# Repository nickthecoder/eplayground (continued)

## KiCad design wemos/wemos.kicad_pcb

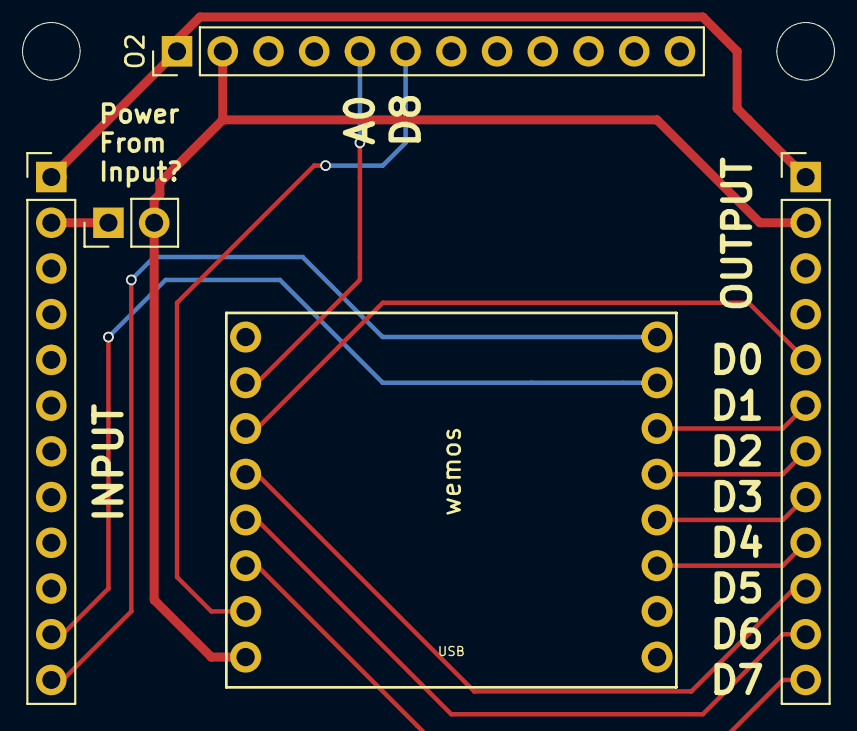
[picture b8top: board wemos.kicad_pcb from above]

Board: 2 copper layers, 7 parts (0 on the bottom side), 16 nets.

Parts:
I1: SerialInput; Socket_Strip_Straight_1x12_Pitch2.54mm
M3, M3#2: MountingHole_3.2mm_M3
O1, O2: Output; Socket_Strip_Straight_1x12_Pitch2.54mm
SW1: SW_SPST; Pin_Header_Straight_1x02_Pitch2.54mm
U1: wemos

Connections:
/A0: O2.5, U1.10
/D0: O1.5, U1.11
/D1: O1.6, U1.6
/D2: O1.7, U1.5
/D3: O1.8, U1.4
/D4: O1.9, U1.3
/D5: O1.10, U1.12
/D6: O1.11, U1.13
/D7: O1.12, U1.14
/D8: O2.6, U1.15
/GND: I1.3, O1.3, O2.3, U1.2
/RX: I1.11, U1.7
/TX: I1.12, U1.8
/VCC: O1.2, O2.2, SW1.2, U1.16
/VIN: I1.1, O1.1, O2.1
unnamed: I1.2, SW1.1

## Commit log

2018-03-31 Added Pro Mini and Nano boards, and power connector.
2018-03-31 Ignoring the library downloaded from github
2018-03-31 Made more room for bare AT chip's crystal.
2018-03-31 Added edge cuts. Plus minor tweaks.
2018-04-01 First version nearly complete, but I'm not happy with it, so I'm going to redsign the layout from scratch.
2018-04-01 Reworked the circuit from scratch.
2018-04-02 Tidy up - Note, there is a problem with VIN.
2018-04-02 More tweaking of the layout.
2018-04-02 Replaced surface mount LEDs with rectangular through hole. Removed PRO-Mini FTDI Header pins from the footprint.
2018-04-02 Fix board size, and moved I2C headers.
2018-04-02 Moved output headers in slightly. Improved text.
2018-04-02 Incfreased resistor size. Improved the ProMini footprint. Removed the VCC LED.
2018-04-02 Changed the directory structure.
2018-04-02 Created a blank and buttons module.
2018-04-02 Tidied up old thinner tracks.
2018-04-03 Sent buttons to DirtyPCB for manufacturing.
2018-04-03 Added a MCP23017 I2C IO Expansion module.
2018-04-04 Added a new "power" and LEDs module (split into two half size modules)
2018-04-04 Tidied up blank, and removed the voltage regulator from "power" module.
2018-04-04 Reworked the ditduino.
2018-04-04 Reworked diyduino module.
2018-04-04 Tidied diyduino
2018-04-04 Added an extra FTDI header, with the RX and TX reversed.
2018-04-04 Reordered serial connectors so that A4 and A5 on the analog connector are in the same place as they are on the serial connector.
2018-04-04 Created blankHalf
2018-04-04 Added buttons and pots modules.
2018-04-05 Combined multiples modules into a single board (called combined).
2018-04-06 Created shift register module (which can act as a master or a slave).
2018-04-06 Rotated the shift register, re-routed the power lines, and added the option of output-enable.
2018-04-06 Created a "prototype" module.
2018-04-06 Reworked the MCP23017 I2C IO Expander module.
2018-04-07 Rotated the TO-220 MOSFETs for better heat dissipation.
2018-04-08 Added a "Blue Pill" module.
2018-04-08 Finished the Blue Pill module.
2018-04-09 "Other" output can have its VCC switched between 5V and 3.3V.
2018-04-09 Rerouted "Serial 2" on Blue Pill module
2018-04-09 Added WeMos module.
2018-04-09 Added Level Converter module.
2018-04-10 Added a multiplexer module (which works in master and slave mode, for up to 40:1 with 5 boards)
2018-04-10 Added I2C header board, which also has an "SPI" OLED header.
2018-04-10 Added a MAX7219 module, which with 8 of the 16 key inputs, and header pins for a 8x6 LED matrix.
2018-04-30 Improved ioExpansion
2018-04-30 Added extra I2C headers to the ioExpansion module.
2018-04-30 Tweaked shift-595
2018-04-30 Reworked shift-595 to include 2 banks of outputs (north and south), and the "next" slave is to the east.
2018-04-30 Created an Arduino Nano board. Reworked the levelConverter, so that it fits on a half-size module, adding triple headers on the other half.
2018-04-30 Added an Arduino ProMini module.
2018-05-01 Added terminal connectors to the header pins half module. Tweaked the MAX7219 module, and added both common anode and common cathode to stripLED modules.
2018-05-01 Removed the 4 button module in favour of the eight button module.
2018-05-01 Tweaked the stripLED module.
2018-05-01 Produced the 2nd batch of gerber files.
2018-05-01 Added pin numbers to Serial pins. M3 hole text now fully inside the edge cuts.
2018-05-01 Added README and LICENSE
2018-05-02 Added a Rotary Encoder module. Tidied up a couple of modules before printing them.
2018-05-02 Ready for the second batch of PCBs to be printed.
2018-05-14 Added a README to multiplexer.
2018-05-15 Added README.md for each of the modules, plus a few minor tweaks to PCB layouts while writing the text.
2018-05-15 Renamed the dual half-sized modules to include both names. Update the READMEs.
2018-05-15 Removed the pcb directory.
2018-05-18 Began fixing eplay component library, and schematics, so that the power pins don't issue warnings.
2018-05-18 More work to ensure there are no errors from KiCAD's schematic checker. Fixed the multiplexer module, so that all 7 slaves will work (only 6 were working, due to a missing VCC to the "Next Output").
2018-05-18 More update to make the libraryies use only relative paths.
2018-10-23 Added MAX7219
